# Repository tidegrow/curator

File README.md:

# Tidegrow Curator

Tidegrow Curator is an experimental WiFi controller for small hydroponic systems.

Curator is responsible for automatically turning on and off the pump and light, and monitoring sensors.

## Firmware

Curator uses the [Tasmota](https://github.com/arendst/Tasmota/) firmware. See the [example rules](curator.rules).

## Pinouts

Curator has two non-standard USB host sockets:

| Signal | Description |
| ------ | ----------- |
| VBUS | Power (5V, 500mA max) |
| D+ | GPIO / Analog input (3.3V) |
| D- | GPIO / Analog input (3.3V) |
| GND | Ground |

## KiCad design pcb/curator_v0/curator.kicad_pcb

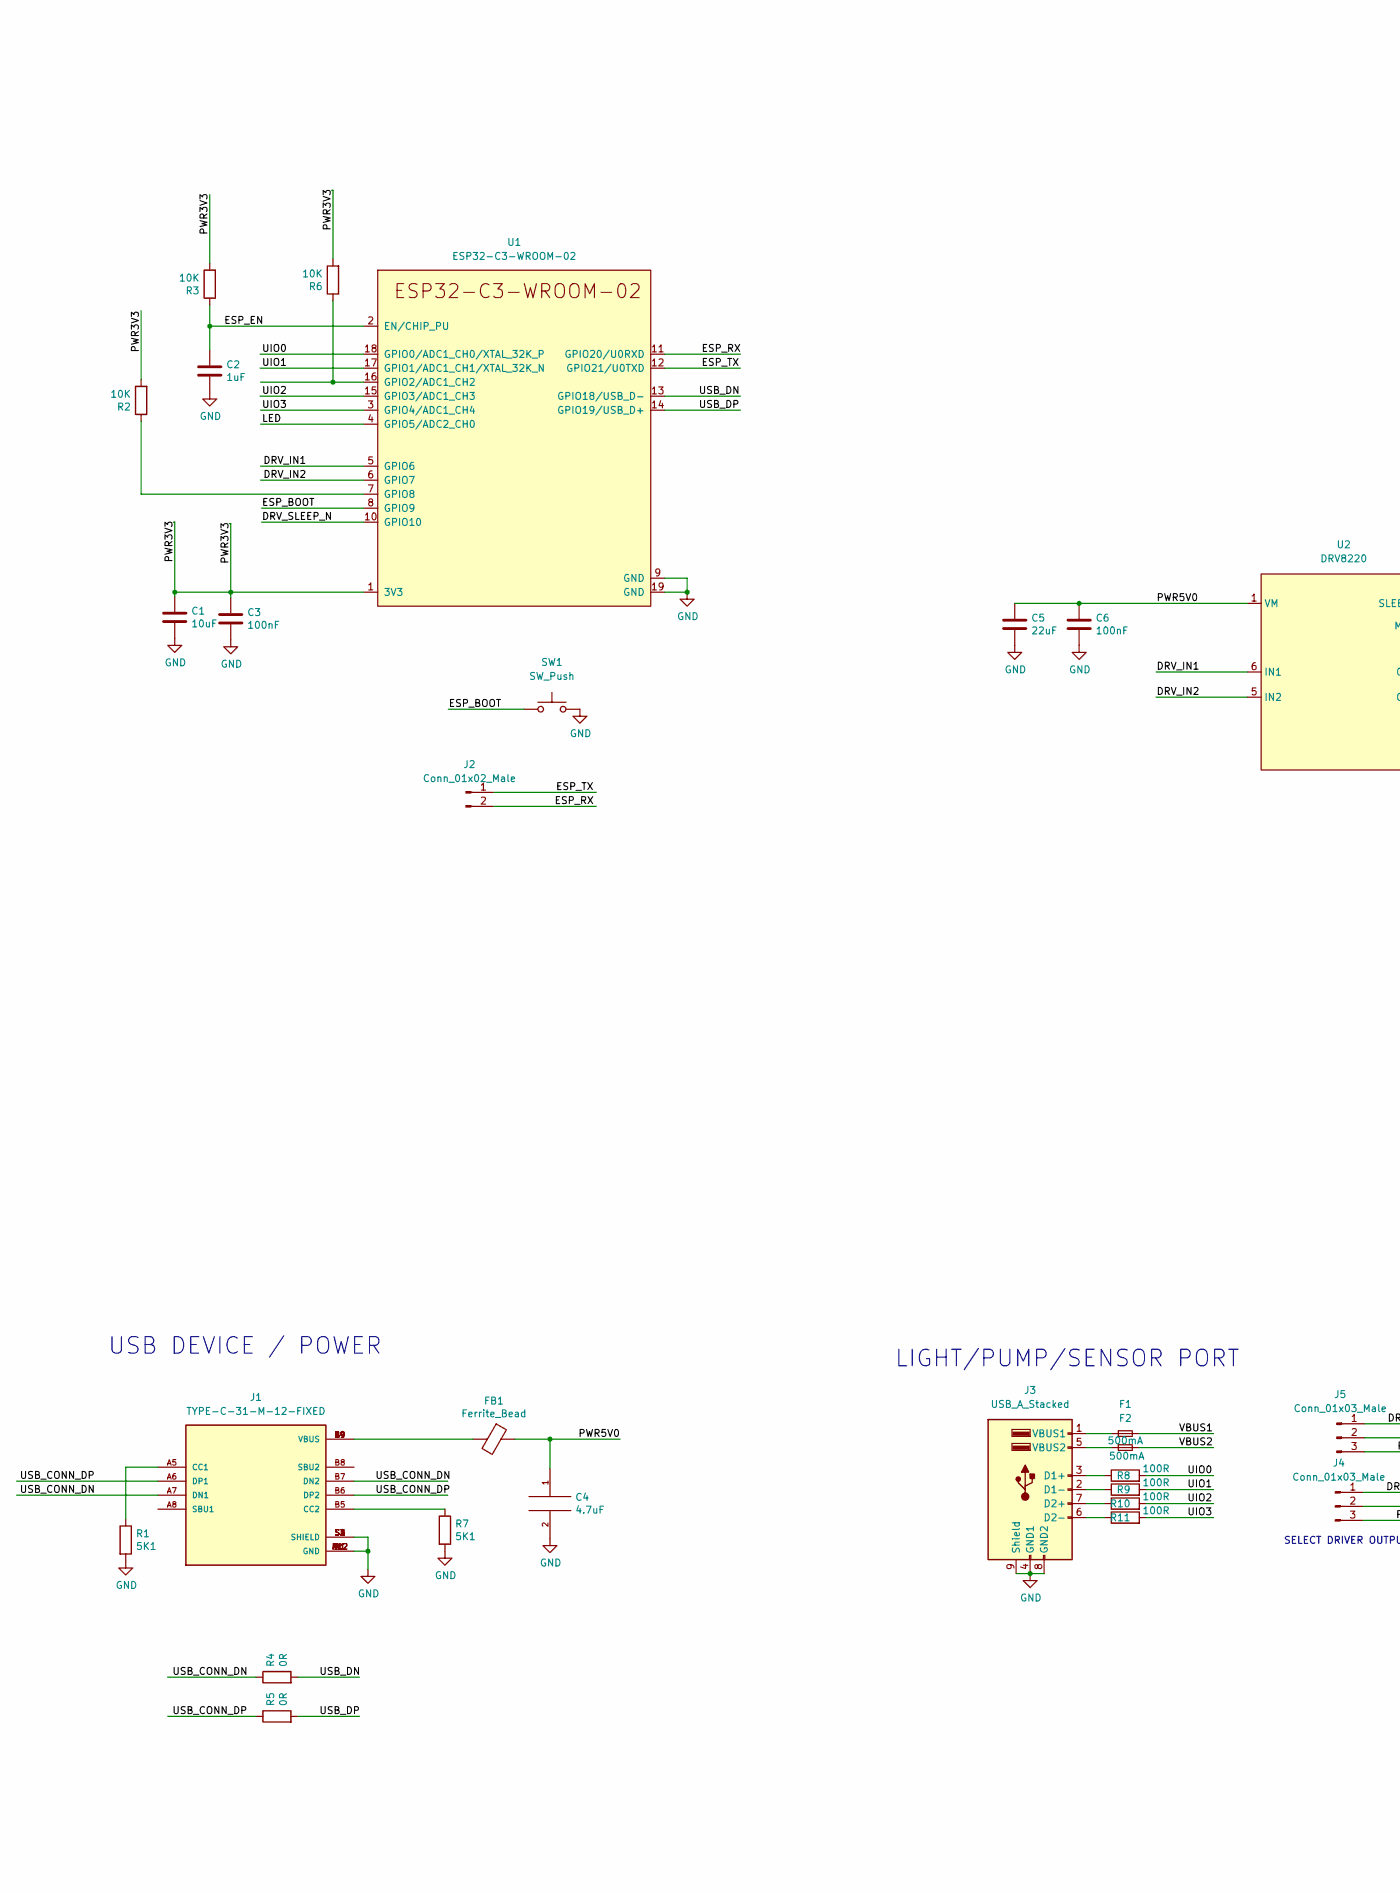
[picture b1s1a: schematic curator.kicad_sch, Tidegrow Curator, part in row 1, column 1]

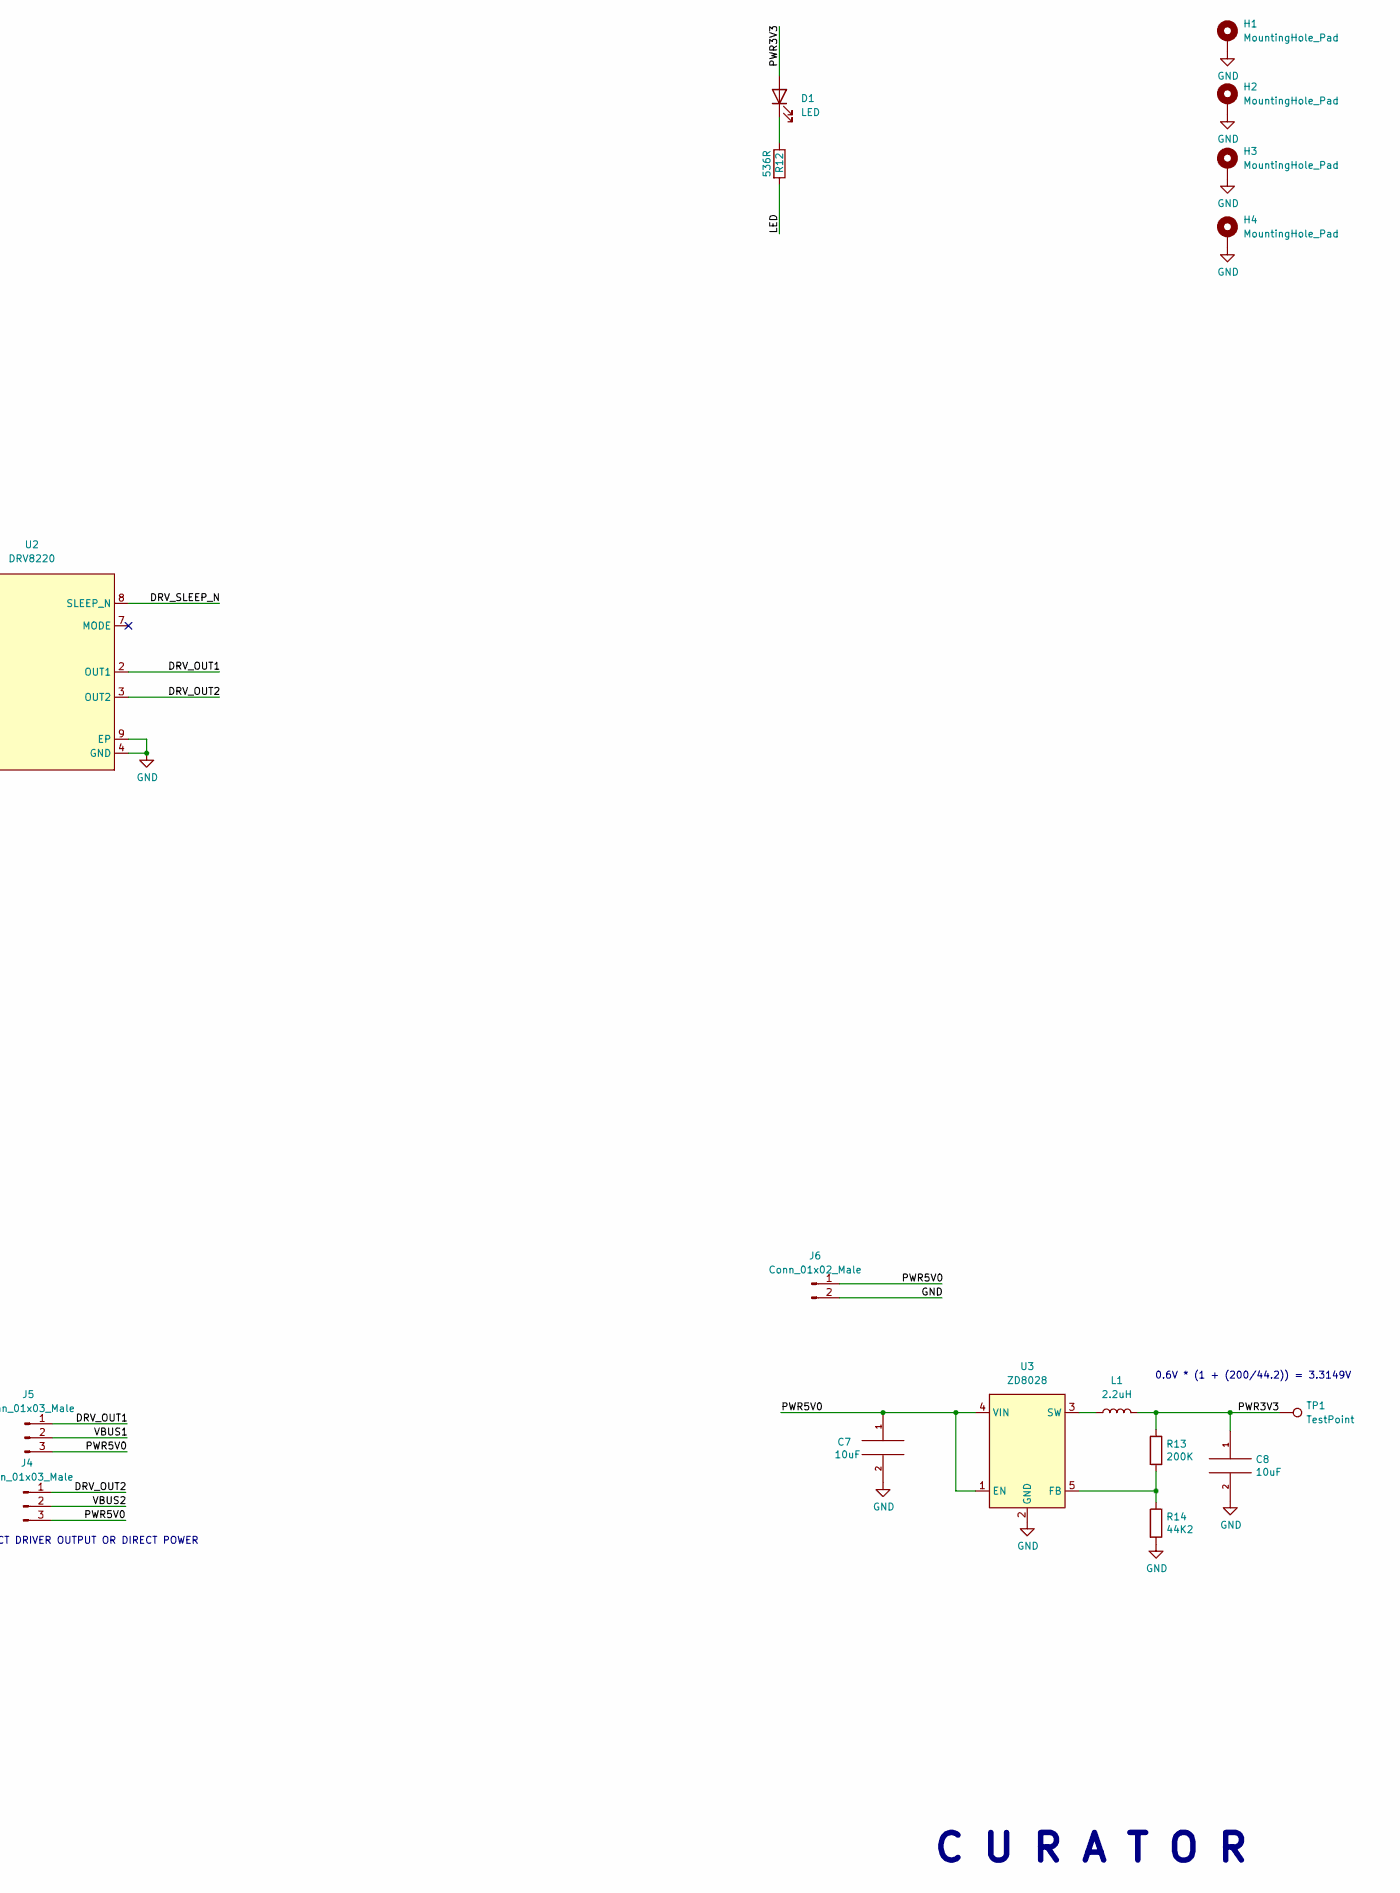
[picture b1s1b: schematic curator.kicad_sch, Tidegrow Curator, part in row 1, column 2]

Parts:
C1: 10uF; R_0603_1608Metric
C2: 1uF; R_0603_1608Metric
C3, C6: 100nF; R_0603_1608Metric
C4: 4.7uF; R_0603_1608Metric
C5: 22uF; R_0603_1608Metric
C7, C8: 10uF; C_0603_1608Metric
D1: LED; LED_0603_1608Metric
F1, F2: 500mA; Fuse_0805_2012Metric
FB1: Ferrite_Bead; R_0603_1608Metric
H1, H2, H3, H4: MountingHole_Pad; MountingHole_3.2mm_M3_Pad
J1: TYPE-C-31-M-12-FIXED; USB_C_Receptacle_HRO_TYPE-C-31-M-12-BIG-PADS; PARTREV A
J2, J6: Conn_01x02_Male; PinHeader_1x02_P2.54mm_Vertical
J3: USB_A_Stacked; USB_A_Wuerth_61400826021_Horizontal_Stacked
J4, J5: Conn_01x03_Male; PinHeader_1x03_P2.54mm_Vertical
L1: 2.2uH; L_0805_2012Metric
R1, R7: 5K1; R_0603_1608Metric
R2, R3, R6: 10K; R_0603_1608Metric
R4, R5: 0R; R_0603_1608Metric
R8, R9, R10, R11: 100R; R_0603_1608Metric
R12: 536R; R_0603_1608Metric
R13: 200K; R_0603_1608Metric
R14: 44K2; R_0603_1608Metric
SW1: SW_Push; Button_2P_3x4mm
TP1: TestPoint; TestPoint_THTPad_D1.0mm_Drill0.5mm
U1: ESP32-C3-WROOM-02
U2: DRV8220; WSON-8-1EP_2x2mm_P0.5mm_EP0.9x1.6mm_ThermalVias
U3: ZD8028; SOT-23-5

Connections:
/DRV_IN1: U1.5 (GPIO6), U2.6 (IN1)
/DRV_IN2: U1.6 (GPIO7), U2.5 (IN2)
/DRV_OUT1: J5.1, U2.2 (OUT1)
/DRV_OUT2: J4.1, U2.3 (OUT2)
/DRV_SLEEP_N: U1.10 (GPIO10), U2.8 (SLEEP_N)
/ESP_BOOT: SW1.1, U1.8 (GPIO9)
/ESP_EN: C2.1, R3.1, U1.2 (EN/CHIP_PU)
/ESP_RX: J2.2, U1.11 (GPIO20/U0RXD)
/ESP_TX: J2.1, U1.12 (GPIO21/U0TXD)
/LED: R12.2, U1.4 (GPIO5/ADC2_CH0)
/PWR3V3: C1.1, C3.1, C8.1, D1.2 (A), L1.2, R2.2, R3.2, R6.2, R13.1, TP1.1, U1.1 (3V3)
/PWR5V0: C4.1, C5.1, C6.1, C7.1, FB1.1, J4.3, J5.3, J6.1, U2.1 (VM), U3.1 (EN), U3.4 (VIN)
/UIO0: R8.2, U1.18 (GPIO0/ADC1_CH0/XTAL_32K_P)
/UIO1: R9.2, U1.17 (GPIO1/ADC1_CH1/XTAL_32K_N)
/UIO2: R10.2, U1.15 (GPIO3/ADC1_CH3)
/UIO3: R11.2, U1.3 (GPIO4/ADC1_CH4)
/USB_CONN_DN: J1.A7 (DN1), J1.B7 (DN2), R4.1
/USB_CONN_DP: J1.A6 (DP1), J1.B6 (DP2), R5.1
/USB_DN: R4.2, U1.13 (GPIO18/USB_D-)
/USB_DP: R5.2, U1.14 (GPIO19/USB_D+)
/VBUS1: F1.2, J5.2
/VBUS2: F2.2, J4.2
GND: C1.2, C2.2, C3.2, C4.2, C5.2, C6.2, C7.2, C8.2, H1.1, H2.1, H3.1, H4.1, J1.A1 (GND), J1.A12 (GND), J1.B1 (GND), J1.B12 (GND), J1.S1 (SHIELD), J1.S2 (SHIELD), J1.S3 (SHIELD), J1.S4 (SHIELD), J3.4 (GND1), J3.8 (GND2), J3.9 (Shield), J6.2, R1.2, R7.2, R14.2, SW1.2, U1.9 (GND), U1.19 (GND), U2.4 (GND), U2.9 (EP), U3.2 (GND)
unnamed: D1.1 (K), R12.1
unnamed: F1.1, J3.1 (VBUS1)
unnamed: F2.1, J3.5 (VBUS2)
unnamed: FB1.2, J1.A4 (VBUS), J1.A9 (VBUS), J1.B4 (VBUS), J1.B9 (VBUS)
unnamed: J1.A5 (CC1), R1.1
unnamed: J1.B5 (CC2), R7.1
unnamed: J3.2 (D1-), R9.1
unnamed: J3.3 (D1+), R8.1
unnamed: J3.6 (D2-), R11.1
unnamed: J3.7 (D2+), R10.1
unnamed: L1.1, U3.3 (SW)
unnamed: R2.1, U1.7 (GPIO8)
unnamed: R6.1, U1.16 (GPIO2/ADC1_CH2)
unnamed: R13.2, R14.1, U3.5 (FB)

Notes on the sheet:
0.6V * (1 + (200/44.2)) = 3.3149V
LIGHT/PUMP/SENSOR PORT
SELECT DRIVER OUTPUT OR DIRECT POWER
USB DEVICE / POWER
C U R A T O R

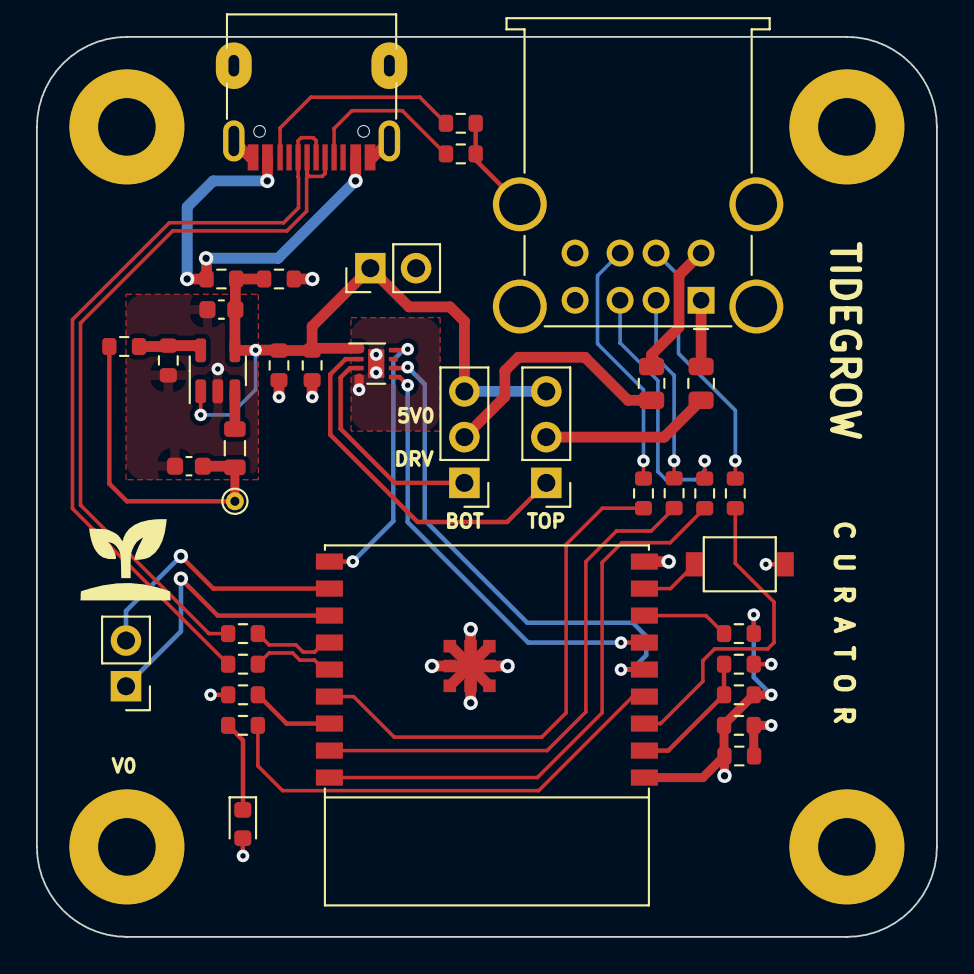
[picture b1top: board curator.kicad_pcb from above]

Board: 2 copper layers, 50.0 x 50.0 mm, 42 parts (0 on the bottom side), 37 nets.

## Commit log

2023-05-20 add pcb

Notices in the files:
pcb/curator_v0/curator.kicad_sch:
Copyright © 2022 Lone Dynamics Corporation
